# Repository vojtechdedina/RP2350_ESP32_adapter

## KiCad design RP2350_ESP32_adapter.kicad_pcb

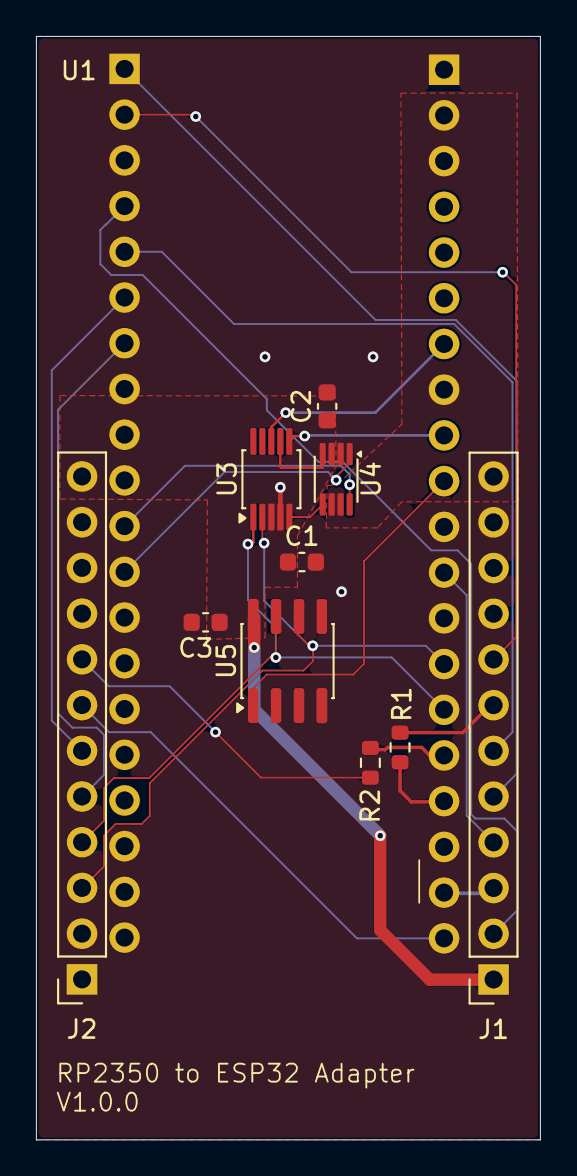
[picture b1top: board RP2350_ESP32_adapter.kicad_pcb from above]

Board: 2 copper layers, 28.0 x 61.3 mm, 11 parts (0 on the bottom side), 25 nets.

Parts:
C1, C2, C3: 100n; C_0603_1608Metric
J1, J2: Conn_01x12_Socket; PinSocket_1x12_P2.54mm_Vertical
R1, R2: 33R; R_0603_1608Metric
U1: RaspberryPi_Pico; RaspberryPi_Pico_Common_THT
U3: EMC2302-1; MSOP-10_3x3mm_P0.5mm
U4: TXU0102-DCU; VSSOP-8_2.3x2mm_P0.5mm
U5: PCA9536D; SOIC-8_3.9x4.9mm_P1.27mm

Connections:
+3V3: C1.1, C2.1, C3.1, J1.1, J2.12, U3.3 (VDD), U4.3 (VCCA), U5.8 (VDD)
+5V: J1.12, U1.39 (VSYS), U4.6 (OE), U4.7 (VCCB)
/LDO_EN: J1.8, U1.2 (GPIO1)
/PWR_EN: J1.5, U1.1 (GPIO0)
/RESET: J1.2, U1.4 (GPIO2)
/RP_PWM1: U1.11 (GPIO8), U4.8 (B1Y)
/RP_PWM2: U1.12 (GPIO9), U4.1 (B2Y)
/RP_TACHO1: U1.32 (GPIO27_ADC1), U3.6 (TACH1)
/RP_TACHO2: U1.34 (GPIO28_ADC2), U3.8 (TACH2)
/RX: J2.5, U1.7 (GPIO5)
/SCL: J2.3, U1.27 (GPIO21), U3.2 (SCL), U5.6 (SCL)
/SDA: J2.4, U1.26 (GPIO20), U3.1 (SDA), U5.7 (SDA)
/TX: J2.6, U1.6 (GPIO4)
/VR_RDY: J1.6, U1.5 (GPIO3)
/W5500_CSN: J1.3, U1.22 (GPIO17)
/W5500_INT_N: J1.4, U1.29 (GPIO22)
/W5500_MISO: J2.7, U1.21 (GPIO16)
/W5500_MOSI: R2.2, U1.25 (GPIO19)
/W5500_RST_N: U1.31 (GPIO26_ADC0), U5.1 (IO0)
/W5500_SCLK: R1.1, U1.24 (GPIO18)
GND: C1.2, C2.2, C3.2, J1.11, J2.1, J2.2, J2.10, J2.11, U1.3 (GND), U1.8 (GND), U1.13 (GND), U1.18 (GND), U1.23 (GND), U1.28 (GND), U1.33 (AGND), U1.38 (GND), U3.4 (GND), U4.2 (GND), U5.4 (VSS)
unnamed: J1.7, R1.2
unnamed: J2.8, R2.1
unnamed: U3.5 (PWM1), U4.5 (A1)
unnamed: U3.7 (PWM2), U4.4 (A2)
